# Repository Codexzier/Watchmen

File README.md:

# Watchmen

Anwendung für den **Arduino UNO Q** (2 GB) mit **UNO Media Carrier** und IMX219-Kamera: Eine
dreh- und neigbare Plattform erkennt **Personen**, **Autos** und ein **markantes Muster**
(ArUco-Marker), folgt Personen bzw. dem Muster mit der Kamera, nutzt ein **AI-Thinker RD-03D**
Human-Radar zur Auswahl der nächsten Person, spart im **Ruhemodus** Strom und wird über Radar oder
Vibration (MPU6050) wieder geweckt. Kalibrierung und Live-Ansicht laufen über eine Webseite, die
der UNO Q selbst ausliefert. Dazu gibt es ein passendes **Shield (KiCad-Projekt)**.

## Inhalt

| Ordner | Inhalt |
|---|---|
| `app.yaml` | App-Beschreibung für Arduino App Lab (Bricks: `web_ui`, `object_detection`) |
| `sketch/` | Mikrocontroller-Teil (STM32U585): Servos, Schrittmotor, Schalter, WS2812B, LED-Matrix, RD-03D, MPU6050, A0 |
| `python/` | Linux-Teil: Zustandsmaschine, Kamera, Erkennung, Nachführung, Radar, Kalibrierung, Webschnittstelle |
| `assets/` | Webseite (Live-Bild, Halbkreis-Radar, Kalibrierung, Einstellungen, Marker-Druck) |
| `hardware/` | Shield für den UNO Q in zwei Versionen (v1 mit, v2 ohne Fenster über der LED-Matrix): Schaltplan, Platine, Gerber – siehe [hardware/README.md](hardware/README.md) |
| `docs/` | [Verdrahtung und Pinbelegung](docs/Verdrahtung.md), Bilder |
| `tests/` | Simulationstests für Sketch, Python-Logik und Webseite |

Der gesamte Code im Sketch und in `python/` ist **Zeile für Zeile auf Deutsch kommentiert**.

## Systemaufbau

```
           Linux (QRB2210, Debian, Python)                       MCU (STM32U585, Zephyr-Sketch)
 ┌───────────────────────────────────────────────┐   Bridge   ┌──────────────────────────────────┐
 │ controller.py  Zustände, Ruhemodus, Ausgaben  │◄──────────►│ Servos (A1, A2) sanft + Ausgleich │
 │ vision.py      Kamera IMX219, ArUco, KI       │  (RPC)     │ 28BYJ-48 + Referenzfahrt (D2)     │
 │ tracker.py     Nachführung (P-Regler)         │            │ WS2812B über SPI-MOSI (D11)       │
 │ radar.py       RD-03D-Ziele, nächste Person   │            │ LED-Matrix-Text / Lauftext        │
 │ calibration.py Kalibrierung 2 (automatisch)   │            │ RD-03D (Serial1, 256000 Baud)     │
 │ webapi.py      Webseite, MJPEG, Marker-PNG    │            │ MPU6050: Vibration + Lage         │
 │ config.py      /app/data/watchmen_config.json │            │ A0: Motoren angeschlossen?        │
 └───────────────────────────────────────────────┘            └──────────────────────────────────┘
        ▲ http://<UNO-Q>:7000 (Socket.IO + MJPEG)
```

Zeitkritisches (Schrittimpulse, Servo-Rampen, LED-Timing, Radar-Protokoll, Vibration) erledigt der
Mikrocontroller. Entscheidungen (Kalibrierung, Erkennung, Ruhemodus) trifft die Linux-Seite.

## Inbetriebnahme

1. **Kamera am Media Carrier aktivieren** (App Lab ≥ Image 523): *Einstellungen (Zahnrad) → Carriers →
   „Enable external carriers …“* einschalten, für **Camera0** `type1-2lanes` (IMX219) wählen,
   *Apply and reboot*.
2. **App auf den UNO Q bringen**, z. B. im Terminal des UNO Q:
   ```bash
   cd ~/ArduinoApps && git clone https://github.com/Codexzier/Watchmen.git watchmen
   ```
   Danach erscheint die App in App Lab unter *My Apps*. Beim ersten Start lädt App Lab die Bricks
   (Webserver, Objekterkennung mit YOLOX-Modell) und die Sketch-Bibliotheken (`Servo`, `ArduinoGraphics`).
3. **Starten** und im Browser `http://<IP-des-UNO-Q>:7000` öffnen.
4. Verdrahtung siehe [docs/Verdrahtung.md](docs/Verdrahtung.md) – mit dem Shield ist alles gesteckt.

## Ablauf und Anzeigen

| Zustand | LED 1 | LED 2 | LED-Matrix |
|---|---|---|---|
| Start / nicht kalibriert / Kalibrierung | rot blinkend | rot blinkend | – |
| Referenzfahrt nach dem Einschalten | türkis blinkend | türkis blinkend | – |
| Kalibrierung abgeschlossen | grün (5 s) | grün (5 s) | – |
| Erkennung aktiv, nichts im Bild | aus | aus | – |
| **Auto** erkannt | **blau** | aus | `CAR` |
| **Person** erkannt (Kamera folgt) | **rot** | aus | `HUMEN` (Lauftext) |
| **Muster** erkannt (Kamera hält es mittig) | weiß | aus | `MARK` |
| **Ruhemodus** (1 min nichts erkannt) | aus | **orange blinkend, 1 Hz** | – |
| **Vibration** über Schwellwert | beide **3× lila** | | |
| Fehler (Schalter nicht gefunden) | rot schnell | rot schnell | `ERR` |

Priorität: **Muster > Person > Auto**. Texte, Schwellwerte usw. sind auf der Webseite einstellbar.

* **Ruhemodus**: Nach 60 s ohne Erkennung wird die Kamera abgeschaltet, Kamera- und Radar-Servo gehen
  waagerecht, die Spulen des Schrittmotors werden stromlos.
* **Aufwachen**: ein Lebewesen im Radar näher als *Weckabstand* (Standard 3 m), mit mindestens
  *Mindestgeschwindigkeit* in *N* Meldungen hintereinander – **oder** eine Vibration über der
  *Vibrationsschwelle* (Standard 150 mg). Beides ist einstellbar.
* **Mehrere Personen**: Die Radar-Ziele werden über ihren Winkel den Personen im Bild zugeordnet; die
  Kamera folgt der **nächsten** Person. Ohne Radar-Zuordnung wird die größte (vermutlich nächste) gewählt.
  Die Webseite zeigt das Radar als Halbkreis mit allen Zielen, der verfolgten Person, dem Kamera-
  Sichtfeld und dem Weckabstand.
* **Deckenmontage** (Sonderpunkt 2): Zeigt der MPU6050 „kopfüber“, wird das Kamerabild um 180°
  gedreht. Die Nachführung rechnet intern im Rohbild weiter, die Kalibrierung bleibt gültig.
* **Ohne Motoren** (Sonderpunkt 1): Liegen an A0 keine 3,3 V an, gibt es keine Kalibrierung und keine
  Bewegung – Erkennung, Anzeige, Ruhemodus und Wecken funktionieren trotzdem.

## Kalibrierung

**Kalibrierung 1 – Bereiche** (Reiter *Kalibrierung*):

1. *Referenzfahrt* drücken: Die Drehachse fährt bis zum Kontaktschalter (= Position 0). Fährt sie in
   die falsche Richtung, *Stopp*, „Drehrichtung umkehren“ setzen und erneut starten.
2. Mit den Schiebereglern Servo 1 (Kamera) und Servo 2 (Radar) bewegen und mit *Aktuell → Minimum /
   Waagerecht / Maximum* die Grenzen übernehmen.
3. Mit den Jog-Tasten die Drehachse an die Grenzen fahren und *Minimum / Grundstellung / Maximum*
   übernehmen.
4. *Ausgleich testen* drücken und Servo 1 bewegen: Das Radar muss waagerecht bleiben. Kippt es mit,
   das Vorzeichen des Ausgleichsfaktors umdrehen.
5. **Einstellungen speichern**.

**Kalibrierung 2 – Richtungen**: Kamera auf eine strukturierte Umgebung richten und
**„Bereit zur Kamerabewegung einstellen“** drücken. Das System dreht und neigt um je 6° hin und zurück
und misst per Phasenkorrelation, wohin und wie weit sich das Bild verschiebt (Richtung *und* Maßstab).
Klappt das (Plausibilitätsprüfung), ist die Kalibrierung abgeschlossen. Sonst die beiden Richtungen
von Hand eintragen und **Speichern** drücken. Danach leuchten beide LEDs 5 s grün und die
Objekterkennung startet.

Nach jedem Einschalten wird bei abgeschlossener Kalibrierung zuerst automatisch die Referenzfahrt
ausgeführt (Offset des Schrittmotors), danach startet die Erkennung.

## Das Muster (ArUco-Marker)

Reiter *Muster*: Marker anzeigen und ausdrucken (Standard: Wörterbuch `DICT_4X4_50`, jede ID). Der
weiße Rand muss erhalten bleiben. Sobald der Marker im Bild ist, hat er Vorrang vor allem anderen.

## Tests (am PC, ohne Hardware)

```bash
# Sketch mit Ersatz-Headern übersetzen und Hardware simulieren (g++)
tests/host_sketch/run_tests.sh

# Python-Logik mit simuliertem Mikrocontroller, Kamera-Welt und KI (numpy, opencv-python-headless, fastapi)
python3 tests/python/test_system.py

# Webseite mit simulierter Hardware ausprobieren (zusätzlich uvicorn, python-socketio)
python3 tests/python/sim_server.py --port 7000     # dann http://localhost:7000

# Browser-Test der Webseite (zusätzlich playwright + Chromium)
python3 tests/python/ui_check.py
```

Abgedeckt sind u. a.: Referenzfahrt inkl. Schrittverlust, Rampen, Servo-Grenzen und Radar-Ausgleich,
RD-03D-Rahmen, WS2812-Bitmuster, Matrix-Text, Vibration, A0-Erkennung; in Python die komplette
Kalibrierung (automatisch und von Hand), Verfolgen von Person und Muster (auch kopfüber), Auswahl der
nächsten Person per Radar, Ruhemodus und Wecken per Radar/Vibration, Betrieb ohne Motoren und Neustart.

## Was vor dem Einsatz am echten Gerät zu prüfen ist

Die Software wurde gegen die offiziellen Quellen (App-Lab-Bricks, Arduino Zephyr-Core,
RouterBridge, Servo-Bibliothek) geschrieben und in Simulationen getestet. Auf echter Hardware
konnte ich sie nicht laufen lassen; ein Übersetzen mit der originalen Arduino-Toolchain war in meiner
Umgebung nicht möglich (Download gesperrt). Besonders beachten:

* Beim ersten Übersetzen in App Lab eventuelle Compiler-Meldungen prüfen.
* **WS2812B**: Das SPI-Timing geht von 5 MHz SPI-Takt aus (SPI2 an 160 MHz). Falsche Farben →
  Pegelwandler und Verdrahtung prüfen.
* **RD-03D**: Seitenrichtung je nach Einbau → ggf. „Radar-X-Achse spiegeln“.
* **MPU6050**: „oben“-Achse passend zur Einbaulage einstellen (siehe Verdrahtung).
* **Shield v1**: Lage des Fensters über der LED-Matrix mit der 1:1-Vorlage prüfen (siehe
  [hardware/README.md](hardware/README.md)). Das Shield v2 hat kein Fenster und verdeckt die Matrix.

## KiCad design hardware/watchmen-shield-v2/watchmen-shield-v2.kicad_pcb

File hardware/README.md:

# Watchmen-Shield (KiCad)

Shield im UNO-Formfaktor für den **Arduino UNO Q** mit allen Anschlüssen des Watchmen-Systems.
Schaltplan und Platine werden vollständig aus `generator/shield_design.py` erzeugt – Bauteile,
Netze und Platzierung stehen nur dort.

## Zwei Versionen

| Version | Ordner | Unterschied |
|---|---|---|
| **v1.0** | `watchmen-shield/` | mit **Fenster** über der LED-Matrix des UNO Q (Matrix bleibt sichtbar) |
| **v2.0** | `watchmen-shield-v2/` | **ohne Fenster** – geschlossene Platine, Masseflächen auch in der Mitte |

Bauteile, Schaltplan, **Pinbelegung** und Platzierung sind bei beiden Versionen identisch; die
Stückliste ist gleich. Bei v2 verdeckt das Shield die LED-Matrix – die Textausgaben
(`CAR`, `HUMEN`, `MARK`, `ERR`) sind dann nur noch auf der Webseite bzw. über die WS2812B-LEDs zu
erkennen. Für v2 entfällt die Fenster-Prüfung mit der 1:1-Vorlage (Punkt 1 unten).

| v1.0 (mit Fenster) | v2.0 (ohne Fenster) |
|---|---|
|  |  |

## Inhalt

Für v2 gelten dieselben Dateien im Ordner `watchmen-shield-v2/` (Dateinamen mit `watchmen-shield-v2`).

| Pfad | Inhalt |
|---|---|
| `watchmen-shield/watchmen-shield.kicad_pro/.kicad_sch/.kicad_pcb` | KiCad-7-Projekt (mit KiCad 7, 8 oder 9 zu öffnen) |
| `watchmen-shield/docs/schaltplan.pdf` · `schaltplan.png` | Schaltplan |
| `watchmen-shield/docs/platine_oben.png` · `platine_unten.png` | Ansicht der Kupferlagen |
| `watchmen-shield/docs/bestueckungsplan.pdf` | Bestückungsplan (Referenzen auf der Fab-Lage) |
| `watchmen-shield/docs/outline_1zu1.pdf` | **1:1-Prüfvorlage** (Kontur, Fenster, Löcher) |
| `watchmen-shield/docs/drc_bericht.txt` | Design-Rule-Check (siehe unten) |
| `watchmen-shield/fabrication/watchmen-shield-gerber.zip` | Gerber + Bohrdaten für den Leiterplattenhersteller |
| `watchmen-shield/fabrication/*-stueckliste.csv` | Stückliste |
| `watchmen-shield/fabrication/*-bestueckung.csv` | Bestückungsdaten (Position/Drehung) |
| `generator/` | Generator-Skripte |

## Eckdaten

* 2 Lagen, 1,6 mm, 68,6 × 53,3 mm (UNO-Kontur), Leiterbahnen ≥ 0,25 mm, Abstände ≥ 0,2 mm,
  Vias 0,6/0,3 mm – bei allen gängigen Herstellern (z. B. JLCPCB, Aisler, PCBWay) im Standardprozess.
* Motor-Versorgung (VMOT) 0,7 mm breit, 5 V und Spulen 0,3 mm, Masse als Kupferfläche auf beiden Seiten.
* SMD-Bauteile in 0805 / SOT-23 / SOIC-16 (handlötbar), Steckverbinder in THT.
* **DRC: 0 Verstöße, 0 offene Verbindungen.** Der Bericht listet zusätzlich nur Hinweise, die in
  der Projektdatei ausgeblendet sind (Bibliotheksvergleich, sich berührende Beschriftungen).

## Vor der Bestellung prüfen (wichtig!)

1. **Fenster für die LED-Matrix (nur v1)**: Das Shield hat einen Ausschnitt (36,5 × 30,5 mm, x = 24,5…61 mm,
   y = 11…41,5 mm von links oben, USB-C links), damit die 13×8-Matrix des UNO Q sichtbar bleibt.
   Die genaue Lage der Matrix konnte ich nicht aus einer Maßzeichnung übernehmen.
   → `docs/outline_1zu1.pdf` in **Originalgröße (100 %)** drucken, ausschneiden, auf den UNO Q legen.
   Passt das Fenster nicht, in `generator/shield_design.py` den Wert `WINDOW` ändern und neu erzeugen.
2. **Löcher H2/H3** liegen (wie beim Original-UNO) sehr nah an den Stiftleisten SCL bzw. A5.
   Dort Kunststoffschrauben/-abstandshalter M2,5–M3 mit kleinem Kopf verwenden.
3. **Höhe**: Das Shield sitzt auf den Buchsenleisten des UNO Q (ca. 8,5 mm). Die Schraubklemme J5
   ragt links 1,3 mm über die Kontur (über der USB-C-Buchse, mechanisch unkritisch).
4. Stiftleisten zum UNO Q mit langen Pins (oder Stapel-Buchsenleisten) verwenden.

## Bestückung – Hinweise

| Teil | Wert | Hinweis |
|---|---|---|
| Q1 | AO3401A (P-MOSFET) | Verpolschutz der Motor-Versorgung |
| F1 | Polyfuse 1812, 2,6–3 A Haltestrom | z. B. Littelfuse 1812L260 oder 1812L300 |
| C1 | 470 µF / ≥ 10 V, Ø 8 mm, RM 3,5 | Polarität beachten (+ markiert) |
| U1 | ULN2003A (SOIC-16) | |
| U2 | 74AHCT1G125 (SOT-23-5) | Pegelwandler für WS2812B – **AHCT**, nicht AHC/LVC |
| D2 | BAT54S | Klemmdiode für A0 |
| R3/R4 | 15 kΩ / 33 kΩ | Teiler VMOT → A0 (5 V → ca. 3,1 V) |
| J6 | JST XH 5-polig (B5B-XH-A) | passt zum Stecker des 28BYJ-48 |
| J11 | Buchsenleiste 1×8 | für GY-521-Modul |
| JP1 | Stiftleiste 1×3 + Jumper | Stellung DIV–A0 = automatische Motorerkennung |
| JP2 | Lötbrücke | normalerweise **offen** lassen |

## Neu erzeugen

Voraussetzungen: KiCad 7 (mit Python-Modul `pcbnew`), Java 25 und
[Freerouting](https://freerouting.app) 2.4 (`freerouting-2.4.1-executable.jar`, z. B. von Maven Central).

```bash
/usr/bin/python3 hardware/generator/build_shield.py \
    --freerouting /pfad/freerouting-2.4.1-executable.jar \
    --java /usr/lib/jvm/java-25-openjdk-amd64/bin/java \
    --variant v1          # v1 = mit Fenster (Standard), v2 = ohne Fenster
```

Die Varianten stehen in `VARIANTS` in `generator/shield_design.py` (Projektname, Revision, Fenster).
Freerouting arbeitet nicht vollständig reproduzierbar: Ein erneuter Lauf ergibt gleichwertige, aber
nicht bitgleiche Leiterbahnen.

Ablauf: Schaltplan schreiben → Netzliste mit `kicad-cli` exportieren und gegen den Entwurf prüfen →
Platine aufbauen (Kontur, Fenster, Bauteile, Netzklassen) → Autorouting (Signale und Versorgung;
Masse wird nicht geroutet) → Masse-Vias an jedem SMD-Masse-Pad, verteilte Vias und Insel-Prüfung →
Masseflächen → DRC → Gerber/Bohrdaten/PDF/SVG. Ohne `--freerouting` bzw. mit `--no-route` entsteht
nur die platzierte, ungeroutete Platine (z. B. um in KiCad von Hand zu routen).

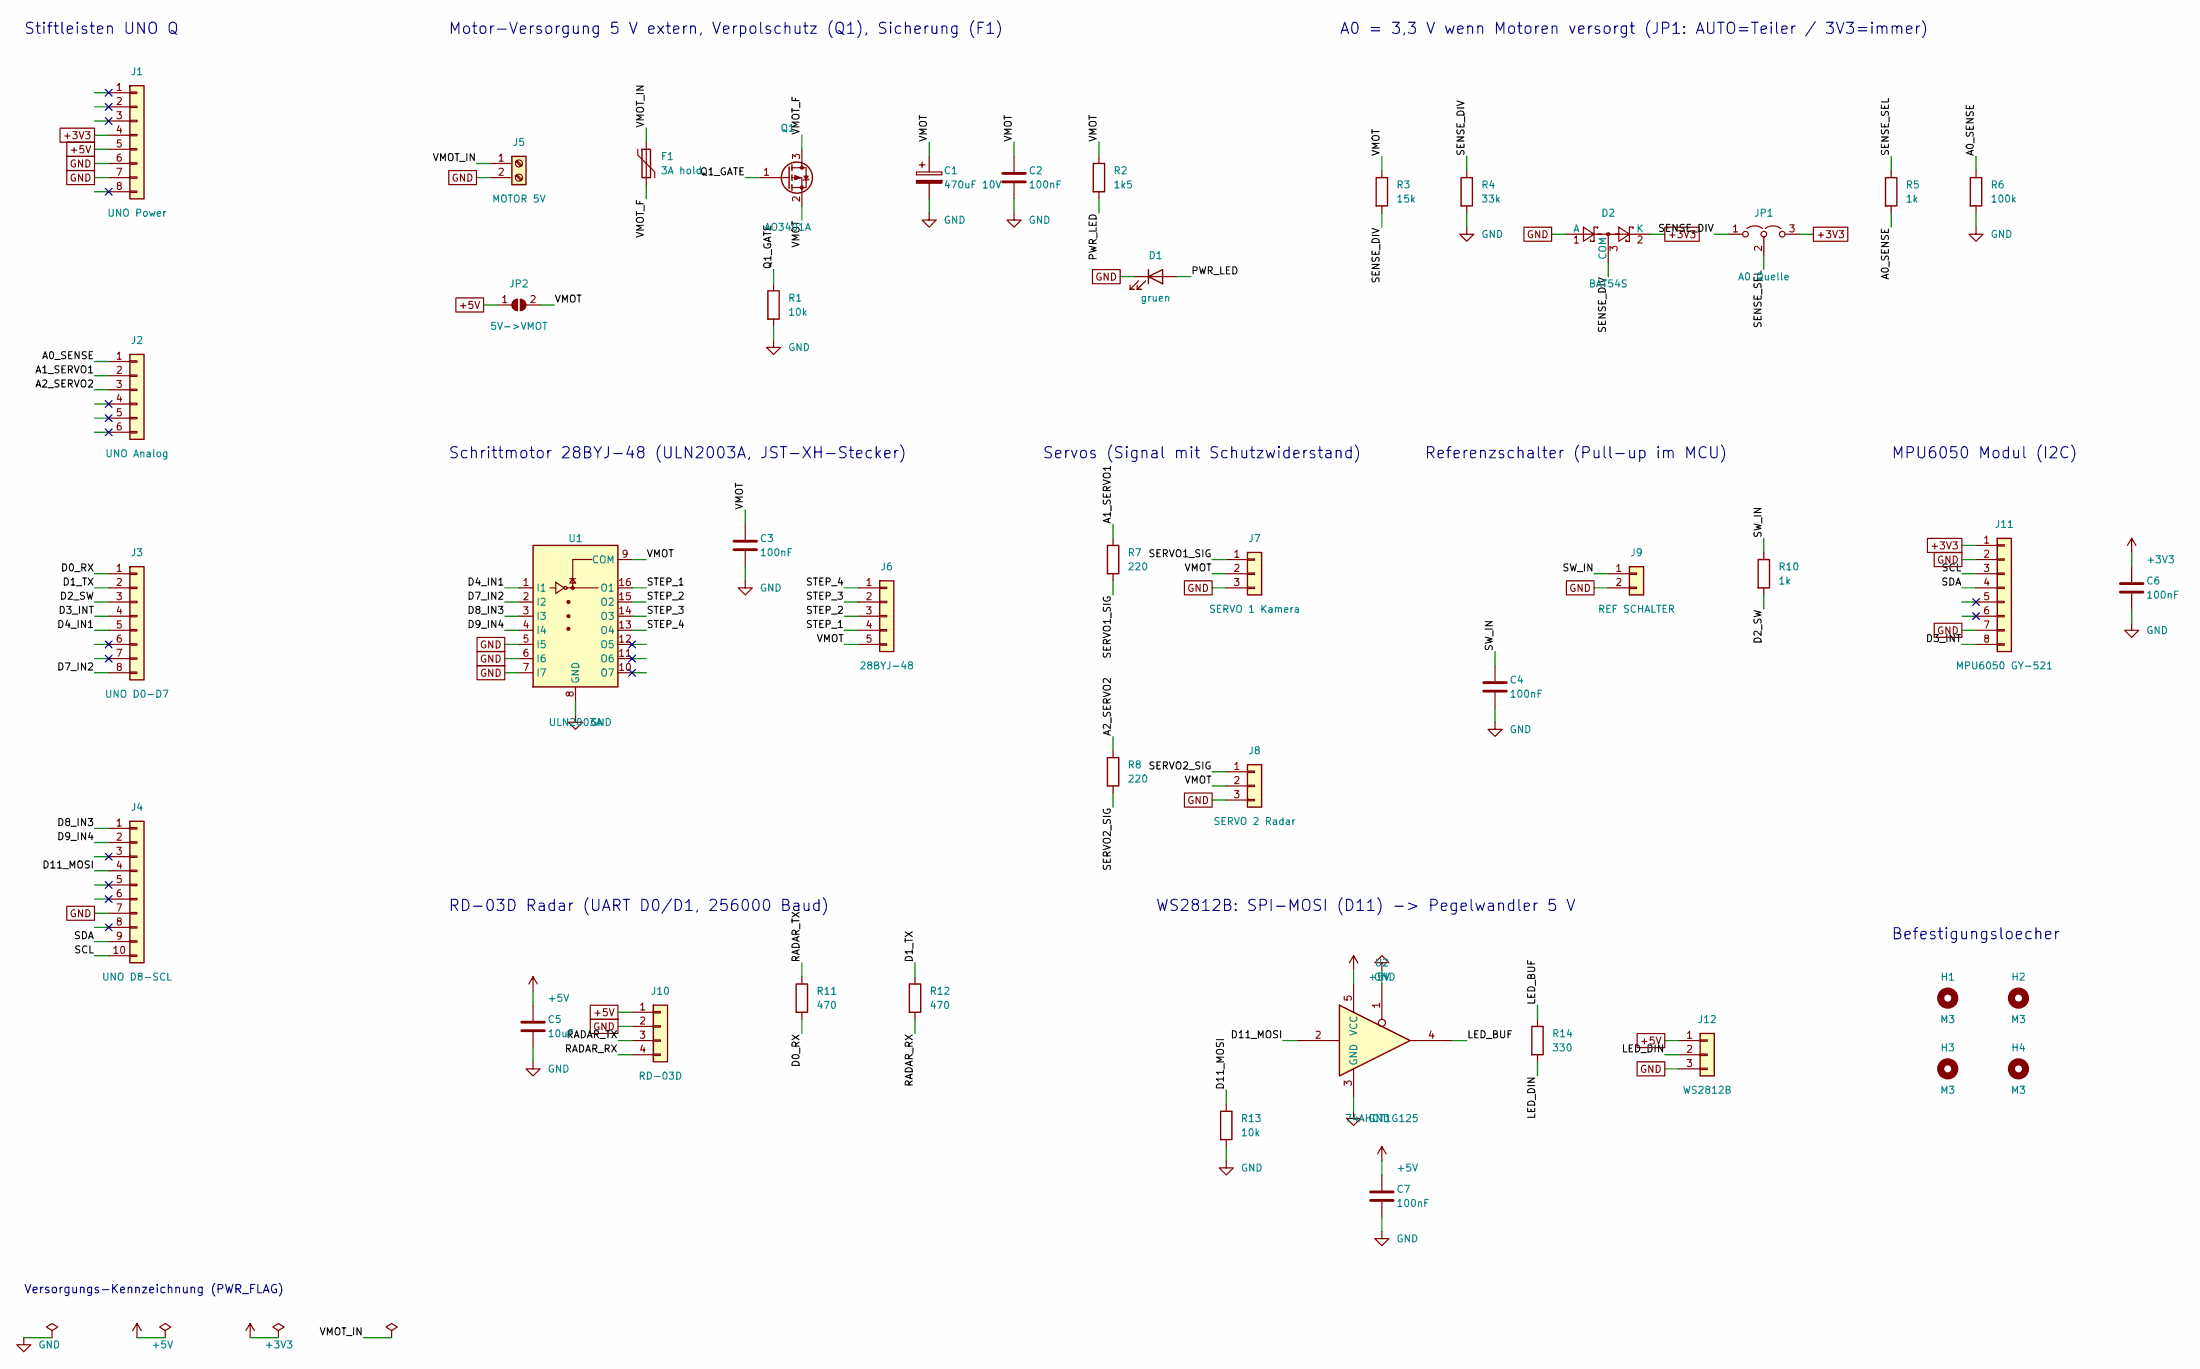
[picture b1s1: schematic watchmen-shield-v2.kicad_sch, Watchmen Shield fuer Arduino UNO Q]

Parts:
C1: 470uF 10V; CP_Radial_D8.0mm_P3.50mm
C2, C3, C4, C6, C7: 100nF; C_0805_2012Metric
C5: 10uF; C_0805_2012Metric
D1: gruen; LED_0805_2012Metric
D2: BAT54S; SOT-23
F1: 3A hold; Fuse_1812_4532Metric
H1, H2, H3, H4: M3; MountingHole_3.2mm_M3
J1: UNO Power; PinHeader_1x08_P2.54mm_Vertical
J2: UNO Analog; PinHeader_1x06_P2.54mm_Vertical
J3: UNO D0-D7; PinHeader_1x08_P2.54mm_Vertical
J4: UNO D8-SCL; PinHeader_1x10_P2.54mm_Vertical
J5: MOTOR 5V; TerminalBlock_Phoenix_MKDS-1,5-2-5.08_1x02_P5.08mm_Horizont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
J6: 28BYJ-48; JST_XH_B5B-XH-A_1x05_P2.50mm_Vertical
J7: SERVO 1 Kamera; PinHeader_1x03_P2.54mm_Vertical
J8: SERVO 2 Radar; PinHeader_1x03_P2.54mm_Vertical
J9: REF SCHALTER; PinHeader_1x02_P2.54mm_Vertical
J10: RD-03D; PinHeader_1x04_P2.54mm_Vertical
J11: MPU6050 GY-521; PinSocket_1x08_P2.54mm_Vertical
J12: WS2812B; PinHeader_1x03_P2.54mm_Vertical
JP1: A0 Quelle; PinHeader_1x03_P2.54mm_Vertical
JP2: 5V->VMOT; SolderJumper-2_P1.3mm_Open_RoundedPad1.0x1.5mm
Q1: AO3401A; SOT-23
R1, R13: 10k; R_0805_2012Metric
R2: 1k5; R_0805_2012Metric
R3: 15k; R_0805_2012Metric
R4: 33k; R_0805_2012Metric
R5, R10: 1k; R_0805_2012Metric
R6: 100k; R_0805_2012Metric
R7, R8: 220; R_0805_2012Metric
R11, R12: 470; R_0805_2012Metric
R14: 330; R_0805_2012Metric
U1: ULN2003A; SOIC-16_3.9x9.9mm_P1.27mm
U2: 74AHCT1G125; SOT-23-5

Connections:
+3V3: C6.1, D2.2 (K), J1.4, J11.1, JP1.3 (B)
+5V: C5.1, C7.1, J1.5, J10.1, J12.1, JP2.1 (A), U2.5 (VCC)
/A0_SENSE: J2.1, R5.2, R6.1
/A1_SERVO1: J2.2, R7.1
/A2_SERVO2: J2.3, R8.1
/D0_RX: J3.1, R11.2
/D1_TX: J3.2, R12.1
/D2_SW: J3.3, R10.2
/D3_INT: J3.4, J11.8
/D4_IN1: J3.5, U1.1 (I1)
/D7_IN2: J3.8, U1.2 (I2)
/D8_IN3: J4.1, U1.3 (I3)
/D9_IN4: J4.2, U1.4 (I4)
/D11_MOSI: J4.4, R13.1, U2.2
/LED_BUF: R14.1, U2.4
/LED_DIN: J12.2, R14.2
/PWR_LED: D1.2 (A), R2.2
/Q1_GATE: Q1.1 (G), R1.1
/RADAR_RX: J10.4, R12.2
/RADAR_TX: J10.3, R11.1
/SCL: J4.10, J11.3
/SDA: J4.9, J11.4
/SENSE_DIV: D2.3 (COM), JP1.1 (A), R3.2, R4.1
/SENSE_SEL: JP1.2 (C), R5.1
/SERVO1_SIG: J7.1, R7.2
/SERVO2_SIG: J8.1, R8.2
/STEP_1: J6.4, U1.16 (O1)
/STEP_2: J6.3, U1.15 (O2)
/STEP_3: J6.2, U1.14 (O3)
/STEP_4: J6.1, U1.13 (O4)
/SW_IN: C4.1, J9.1, R10.1
/VMOT: C1.1, C2.1, C3.1, J6.5, J7.2, J8.2, JP2.2 (B), Q1.2 (S), R2.1, R3.1, U1.9 (COM)
/VMOT_F: F1.2, Q1.3 (D)
/VMOT_IN: F1.1, J5.1
GND: C1.2, C2.2, C3.2, C4.2, C5.2, C6.2, C7.2, D1.1 (K), D2.1 (A), J1.6, J1.7, J4.7, J5.2, J7.3, J8.3, J9.2, J10.2, J11.2, J11.7, J12.3, R1.2, R4.2, R6.2, R13.2, U1.5 (I5), U1.6 (I6), U1.7 (I7), U1.8 (GND), U2.1, U2.3 (GND)

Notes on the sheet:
Stiftleisten UNO Q
Motor-Versorgung 5 V extern, Verpolschutz (Q1), Sicherung (F1)
A0 = 3,3 V wenn Motoren versorgt (JP1: AUTO=Teiler / 3V3=immer)
Schrittmotor 28BYJ-48 (ULN2003A, JST-XH-Stecker)
Servos (Signal mit Schutzwiderstand)
Referenzschalter (Pull-up im MCU)
MPU6050 Modul (I2C)
RD-03D Radar (UART D0/D1, 256000 Baud)
WS2812B: SPI-MOSI (D11) -> Pegelwandler 5 V
Befestigungsloecher
Versorgungs-Kennzeichnung (PWR_FLAG)

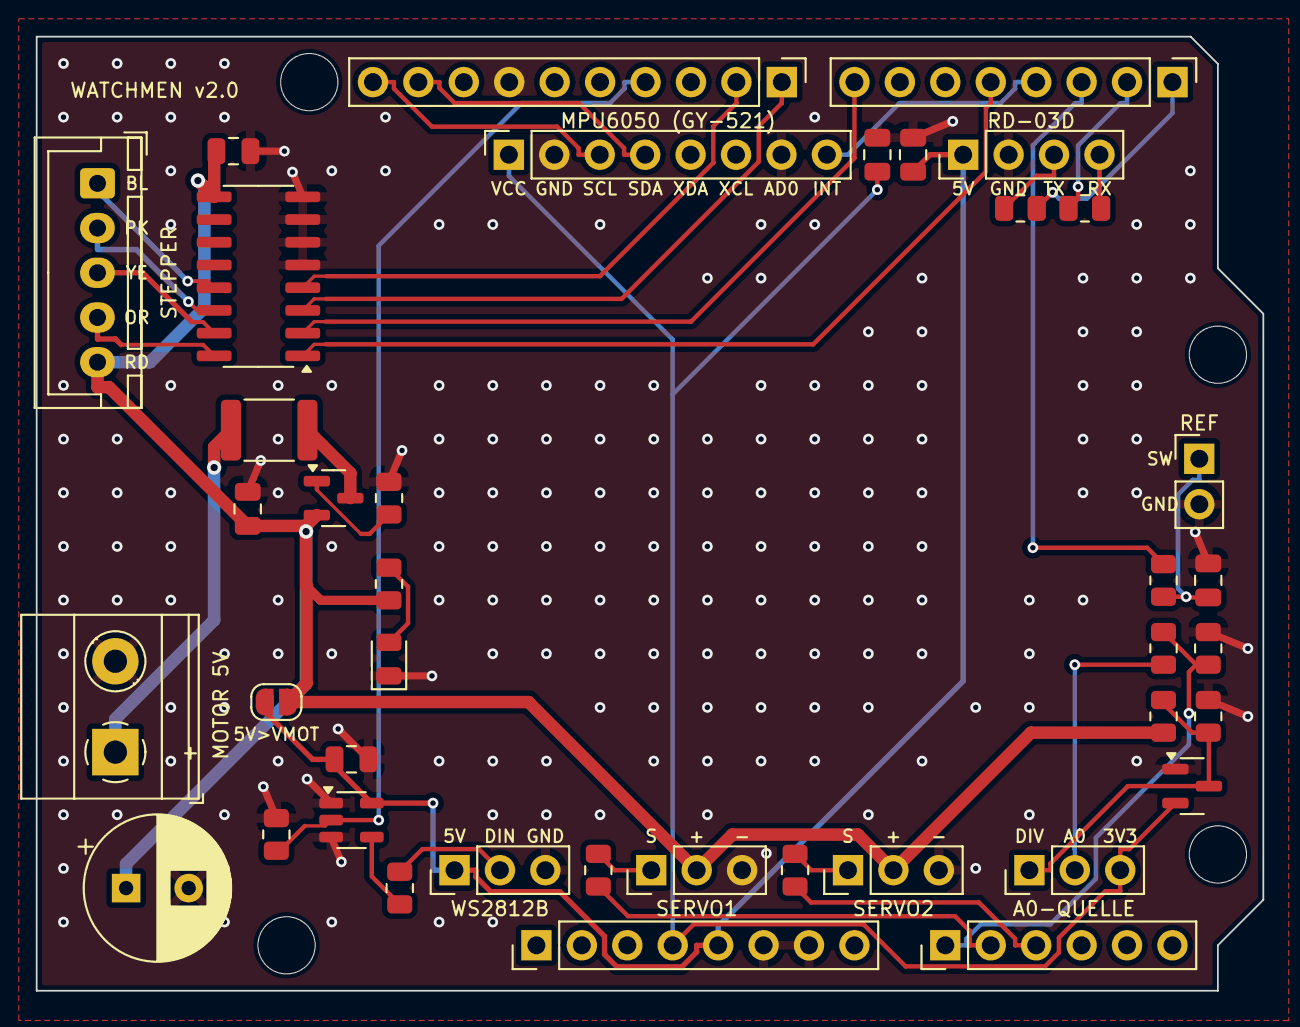
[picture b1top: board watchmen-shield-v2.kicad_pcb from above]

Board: 2 copper layers, 68.6 x 53.3 mm, 44 parts (0 on the bottom side), 35 nets.

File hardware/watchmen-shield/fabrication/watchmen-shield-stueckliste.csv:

Anzahl;Referenzen;Wert;Footprint;Symbol
1;C1;470uF 10V;Capacitor_THT:CP_Radial_D8.0mm_P3.50mm;Device:C_Polarized
5;C2,C3,C4,C6,C7;100nF;Capacitor_SMD:C_0805_2012Metric;Device:C
1;C5;10uF;Capacitor_SMD:C_0805_2012Metric;Device:C
1;D1;gruen;LED_SMD:LED_0805_2012Metric;Device:LED
1;D2;BAT54S;Package_TO_SOT_SMD:SOT-23;Diode:BAT54S
1;F1;3A hold;Fuse:Fuse_1812_4532Metric;Device:Polyfuse
4;H1,H2,H3,H4;M3;MountingHole:MountingHole_3.2mm_M3;Mechanical:MountingHole
1;J1;UNO Power;Connector_PinHeader_2.54mm:PinHeader_1x08_P2.54mm_Vertical;Connector_Generic:Conn_01x08
1;J10;RD-03D;Connector_PinHeader_2.54mm:PinHeader_1x04_P2.54mm_Vertical;Connector_Generic:Conn_01x04
1;J11;MPU6050 GY-521;Connector_PinSocket_2.54mm:PinSocket_1x08_P2.54mm_Vertical;Connector_Generic:Conn_01x08
1;J12;WS2812B;Connector_PinHeader_2.54mm:PinHeader_1x03_P2.54mm_Vertical;Connector_Generic:Conn_01x03
1;J2;UNO Analog;Connector_PinHeader_2.54mm:PinHeader_1x06_P2.54mm_Vertical;Connector_Generic:Conn_01x06
1;J3;UNO D0-D7;Connector_PinHeader_2.54mm:PinHeader_1x08_P2.54mm_Vertical;Connector_Generic:Conn_01x08
1;J4;UNO D8-SCL;Connector_PinHeader_2.54mm:PinHeader_1x10_P2.54mm_Vertical;Connector_Generic:Conn_01x10
1;J5;MOTOR 5V;TerminalBlock_Phoenix:TerminalBlock_Phoenix_MKDS-1,5-2-5.08_1x02_P5.08mm_Horizontal;Connector:Screw_Terminal_01x02
1;J6;28BYJ-48;Connector_JST:JST_XH_B5B-XH-A_1x05_P2.50mm_Vertical;Connector_Generic:Conn_01x05
1;J7;SERVO 1 Kamera;Connector_PinHeader_2.54mm:PinHeader_1x03_P2.54mm_Vertical;Connector_Generic:Conn_01x03
1;J8;SERVO 2 Radar;Connector_PinHeader_2.54mm:PinHeader_1x03_P2.54mm_Vertical;Connector_Generic:Conn_01x03
1;J9;REF SCHALTER;Connector_PinHeader_2.54mm:PinHeader_1x02_P2.54mm_Vertical;Connector_Generic:Conn_01x02
1;JP1;A0 Quelle;Connector_PinHeader_2.54mm:PinHeader_1x03_P2.54mm_Vertical;Jumper:Jumper_3_Open
1;JP2;5V->VMOT;Jumper:SolderJumper-2_P1.3mm_Open_RoundedPad1.0x1.5mm;Jumper:SolderJumper_2_Open
1;Q1;AO3401A;Package_TO_SOT_SMD:SOT-23;Transistor_FET:AO3401A
2;R1,R13;10k;Resistor_SMD:R_0805_2012Metric;Device:R
2;R11,R12;470;Resistor_SMD:R_0805_2012Metric;Device:R
1;R14;330;Resistor_SMD:R_0805_2012Metric;Device:R
1;R2;1k5;Resistor_SMD:R_0805_2012Metric;Device:R
1;R3;15k;Resistor_SMD:R_0805_2012Metric;Device:R
1;R4;33k;Resistor_SMD:R_0805_2012Metric;Device:R
2;R5,R10;1k;Resistor_SMD:R_0805_2012Metric;Device:R
1;R6;100k;Resistor_SMD:R_0805_2012Metric;Device:R
2;R7,R8;220;Resistor_SMD:R_0805_2012Metric;Device:R
1;U1;ULN2003A;Package_SO:SOIC-16_3.9x9.9mm_P1.27mm;Transistor_Array:ULN2003A
1;U2;74AHCT1G125;Package_TO_SOT_SMD:SOT-23-5;74xGxx:74AHCT1G125

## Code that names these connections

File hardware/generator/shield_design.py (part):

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         pins={1: None, 2: None, 3: None, 4: "+3V3", 5: "+5V", 6: "GND", 7: "GND", 8: None},
         sch=(40.64, 50.8), pcb=(27.94, 50.80, 90), labels="NC IOR RST 3V3 5V GND GND VIN"),
    dict(ref="J2", sym="Connector_Generic:Conn_01x06", value="UNO Analog", fp=HDR.format(n=6),
         pins={1: "A0_SENSE", 2: "A1_SERVO1", 3: "A2_SERVO2", 4: None, 5: None, 6: None},
         sch=(40.64, 96.52), pcb=(50.80, 50.80, 90), labels="A0 A1 A2 A3 A4 A5"),
    dict(ref="J3", sym="Connector_Generic:Conn_01x08", value="UNO D0-D7", fp=HDR.format(n=8),
         pins={1: "D0_RX", 2: "D1_TX", 3: "D2_SW", 4: "D3_INT", 5: "D4_IN1", 6: None, 7: None, 8: "D7_IN2"},
         sch=(40.64, 137.16), pcb=(63.50, 2.54, -90), labels="D0 D1 D2 D3 D4 D5 D6 D7"),
    dict(ref="J4", sym="Connector_Generic:Conn_01x10", value="UNO D8-SCL", fp=HDR.format(n=10),
         pins={1: "D8_IN3", 2: "D9_IN4", 3: None, 4: "D11_MOSI", 5: None, 6: None, 7: "GND", 8: None, 9: "SDA", 10: "SCL"},
         sch=(40.64, 185.42), pcb=(41.66, 2.54, -90), labels="D8 D9 D10 D11 D12 D13 GND ARF SDA SCL"),

    # ---------------- Motor-Stromversorgung (extern 5 V) mit Verpolschutz --------------
    dict(ref="J5", sym="Connector:Screw_Terminal_01x02", value="MOTOR 5V",
         fp="TerminalBlock_Phoenix:TerminalBlock_Phoenix_MKDS-1,5-2-5.08_1x02_P5.08mm_Horizontal",
         pins={1: "VMOT_IN", 2: "GND"}, sch=(109.22, 55.88), pcb=(4.4, 40.0, 90)),
    dict(ref="F1", sym="Device:Polyfuse", value="3A hold", fp="Fuse:Fuse_1812_4532Metric",
         pins={1: "VMOT_IN", 2: "VMOT_F"}, sch=(132.08, 55.88), pcb=(13.0, 22.0, 0)),
    dict(ref="Q1", sym="Transistor_FET:AO3401A", value="AO3401A", fp="Package_TO_SOT_SMD:SOT-23",
         pins={1: "Q1_GATE", 2: "VMOT", 3: "VMOT_F"}, sch=(157.48, 58.42), pcb=(16.6, 25.8, 0)),
    dict(ref="R1", sym="Device:R", value="10k", fp=R0805, pins={1: "Q1_GATE", 2: "GND"},
         sch=(154.94, 81.28), pcb=(19.7, 25.8, 90)),
    dict(ref="C1", sym="Device:C_Polarized", value="470uF 10V", fp="Capacitor_THT:CP_Radial_D8.0mm_P3.50mm",
         pins={1: "VMOT", 2: "GND"}, sch=(182.88, 58.42), pcb=(5.0, 47.6, 0)),
    dict(ref="C2", sym="Device:C", value="100nF", fp=C0805, pins={1: "VMOT", 2: "GND"},
         sch=(198.12, 58.42), pcb=(11.8, 26.4, 90)),
    dict(ref="R2", sym="Device:R", value="1k5", fp=R0805, pins={1: "VMOT", 2: "PWR_LED"},
         sch=(213.36, 58.42), pcb=(19.7, 30.6, 90)),
    dict(ref="D1", sym="Device:LED", value="gruen", fp="LED_SMD:LED_0805_2012Metric",
         pins={1: "GND", 2: "PWR_LED"}, sch=(223.52, 76.2), pcb=(19.7, 34.8, 90)),
    dict(ref="JP2", sym="Jumper:SolderJumper_2_Open", value="5V->VMOT",
         fp="Jumper:SolderJumper-2_P1.3mm_Open_RoundedPad1.0x1.5mm",
         pins={1: "+5V", 2: "VMOT"}, sch=(109.22, 81.28), pcb=(13.4, 37.2, 0)),

    # ---------------- A0: Motoren angeschlossen? ----------------------------------------
    dict(ref="R3", sym="Device:R", value="15k", fp=R0805, pins={1: "VMOT", 2: "SENSE_DIV"},
         sch=(264.16, 60.96), pcb=(63.0, 38.0, 90)),
    dict(ref="R4", sym="Device:R", value="33k", fp=R0805, pins={1: "SENSE_DIV", 2: "GND"},
         sch=(279.4, 60.96), pcb=(65.5, 38.0, 90)),
    dict(ref="D2", sym="Diode:BAT54S", value="BAT54S", fp="Package_TO_SOT_SMD:SOT-23",
         pins={1: "GND", 2: "+3V3", 3: "SENSE_DIV"}, sch=(304.8, 68.58), pcb=(64.6, 41.9, 0)),
    dict(ref="JP1", sym="Jumper:Jumper_3_Open", value="A0 Quelle", fp=HDR.format(n=3),
         pins={1: "SENSE_DIV", 2: "SENSE_SEL", 3: "+3V3"}, sch=(332.74, 68.58), pcb=(55.5, 46.6, 90),
         labels="DIV A0 3V3"),
    dict(ref="R5", sym="Device:R", value="1k", fp=R0805, pins={1: "SENSE_SEL", 2: "A0_SENSE"},
         sch=(355.6, 60.96), pcb=(63.0, 34.2, 90)),
    dict(ref="R6", sym="Device:R", value="100k", fp=R0805, pins={1: "A0_SENSE", 2: "GND"},
         sch=(370.84, 60.96), pcb=(65.5, 34.2, 90)),

    # ---------------- Schrittmotor 28BYJ-48 (ULN2003A auf dem Shield) ------------------
    dict(ref="U1", sym="Transistor_Array:ULN2003A", value="ULN2003A", fp="Package_SO:SOIC-16_3.9x9.9mm_P1.27mm",
         pins={1: "D4_IN1", 2: "D7_IN2", 3: "D8_IN3", 4: "D9_IN4", 5: "GND", 6: "GND", 7: "GND", 8: "GND",
               9: "VMOT", 10: None, 11: None, 12: None, 13: "STEP_4", 14: "STEP_3", 15: "STEP_2", 16: "STEP_1"},
         sch=(119.38, 137.16), pcb=(12.4, 13.4, 180)),
    dict(ref="C3", sym="Device:C", value="100nF", fp=C0805, pins={1: "VMOT", 2: "GND"},
         sch=(149.86, 124.46), pcb=(11.0, 6.4, 0)),
    dict(ref="J6", sym="Connector_Generic:Conn_01x05", value="28BYJ-48",
         fp="Connector_JST:JST_XH_B5B-XH-A_1x05_P2.50mm_Vertical",
         pins={1: "STEP_4", 2: "STEP_3", 3: "STEP_2", 4: "STEP_1", 5: "VMOT"}, sch=(175.26, 137.16), pcb=(3.4, 8.2, -90),
         labels="BL PK YE OR RD"),

    # ---------------- Servos ------------------------------------------------------------
    dict(ref="R7", sym="Device:R", value="220", fp=R0805, pins={1: "A1_SERVO1", 2: "SERVO1_SIG"},
         sch=(215.9, 127.0), pcb=(31.4, 46.6, 90)),
    dict(ref="J7", sym="Connector_Generic:Conn_01x03", value="SERVO 1 Kamera", fp=HDR.format(n=3),
         pins={1: "SERVO1_SIG", 2: "VMOT", 3: "GND"}, sch=(241.3, 129.54), pcb=(34.36, 46.6, 90), labels="S + -"),
    dict(ref="R8", sym="Device:R", value="220", fp=R0805, pins={1: "A2_SERVO2", 2: "SERVO2_SIG"},
         sch=(215.9, 165.1), pcb=(42.4, 46.6, 90)),
    dict(ref="J8", sym="Connector_Generic:Conn_01x03", value="SERVO 2 Radar", fp=HDR.format(n=3),
         pins={1: "SERVO2_SIG", 2: "VMOT", 3: "GND"}, sch=(241.3, 167.64), pcb=(45.36, 46.6, 90), labels="S + -"),

    # ---------------- Kontaktschalter (Referenz der Drehachse) ---------------------------
    dict(ref="J9", sym="Connector_Generic:Conn_01x02", value="REF SCHALTER", fp=HDR.format(n=2),
         pins={1: "SW_IN", 2: "GND"}, sch=(309.88, 129.54), pcb=(65.0, 23.6, 0), labels="SW GND"),
    dict(ref="R10", sym="Device:R", value="1k", fp=R0805, pins={1: "SW_IN", 2: "D2_SW"},
         sch=(332.74, 129.54), pcb=(63.0, 30.4, 90)),
    dict(ref="C4", sym="Device:C", value="100nF", fp=C0805, pins={1: "SW_IN", 2: "GND"},
         sch=(284.48, 149.86), pcb=(65.5, 30.4, 90)),

    # ---------------- AI-Thinker RD-03D (UART 256000 Baud) -------------------------------
    dict(ref="J10", sym="Connector_Generic:Conn_01x04", value="RD-03D", fp=HDR.format(n=4),
         pins={1: "+5V", 2: "GND", 3: "RADAR_TX", 4: "RADAR_RX"}, sch=(134.62, 210.82), pcb=(51.8, 6.6, 90),
         labels="5V GND TX RX"),
    dict(ref="R11", sym="Device:R", value="470", fp=R0805, pins={1: "RADAR_TX", 2: "D0_RX"},
         sch=(160.02, 205.74), pcb=(55.0, 9.6, 0)),
    dict(ref="R12", sym="Device:R", value="470", fp=R0805, pins={1: "D1_TX", 2: "RADAR_RX"},
         sch=(180.34, 205.74), pcb=(58.6, 9.6, 0)),
    dict(ref="C5", sym="Device:C", value="10uF", fp=C0805, pins={1: "+5V", 2: "GND"},
         sch=(111.76, 210.82), pcb=(49.0, 6.6, 90)),
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    # ---------------- MPU6050 (Modul GY-521 in Buchsenleiste) ----------------------------
    dict(ref="J11", sym="Connector_Generic:Conn_01x08", value="MPU6050 GY-521",
         fp="Connector_PinSocket_2.54mm:PinSocket_1x08_P2.54mm_Vertical",
         pins={1: "+3V3", 2: "GND", 3: "SCL", 4: "SDA", 5: None, 6: None, 7: "GND", 8: "D3_INT"},
         sch=(375.92, 132.08), pcb=(26.4, 6.6, 90), labels="VCC GND SCL SDA XDA XCL AD0 INT"),
    dict(ref="C6", sym="Device:C", value="100nF", fp=C0805, pins={1: "+3V3", 2: "GND"},
         sch=(398.78, 132.08), pcb=(47.0, 6.6, 90)),

    # ---------------- WS2812B (Datenleitung über Pegelwandler 3,3 V → 5 V) --------------
    dict(ref="U2", sym="74xGxx:74AHCT1G125", value="74AHCT1G125", fp="Package_TO_SOT_SMD:SOT-23-5",
         pins={1: "GND", 2: "D11_MOSI", 3: "GND", 4: "LED_BUF", 5: "+5V"}, sch=(264.16, 213.36), pcb=(17.6, 43.8, 0)),
    dict(ref="R13", sym="Device:R", value="10k", fp=R0805, pins={1: "D11_MOSI", 2: "GND"},
         sch=(236.22, 228.6), pcb=(13.4, 44.6, 90)),
    dict(ref="R14", sym="Device:R", value="330", fp=R0805, pins={1: "LED_BUF", 2: "LED_DIN"},
         sch=(292.1, 213.36), pcb=(20.3, 47.6, 90)),
    dict(ref="C7", sym="Device:C", value="100nF", fp=C0805, pins={1: "+5V", 2: "GND"},
         sch=(264.16, 241.3), pcb=(17.6, 40.4, 0)),
    dict(ref="J12", sym="Connector_Generic:Conn_01x03", value="WS2812B", fp=HDR.format(n=3),
         pins={1: "+5V", 2: "LED_DIN", 3: "GND"}, sch=(322.58, 215.9), pcb=(23.36, 46.6, 90), labels="5V DIN GND"),

    # ---------------- Befestigungslöcher -----------------------------------------------
    dict(ref="H1", sym="Mechanical:MountingHole", value="M3", fp="MountingHole:MountingHole_3.2mm_M3",
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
